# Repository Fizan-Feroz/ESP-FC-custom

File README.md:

# ESP-FC Flight Controller

The mini, DIY, Low cost, ESP32 based, high performance flight controller for hobbyists.

# Features

* Espressif targets (ESP32, ESP32-S3)
* ESC protocols (PWM, Oneshot125/42, Multishot, Brushed, Dshot150/300/600 bidirectional)
* PPM, SBUS, IBUS and CRSF Receivers
* Builtin ESP-NOW receiver and WiFi configuration [read more...](/docs/wireless.md)
* SPI and I2C gyro modules support (MPU6050, MPU9250, ICM20602, ICM42688, BMI160)
* Flight modes (ACRO, ANGLE, AIRMODE)
* Frames (Quad X)
* Betaflight configuration tool compatible (v10.10)
* Configurable Gyro Filters (LPF, Dynamic Notches, dTerm, RPM)
* Blackbox recording (OpenLog/OpenLager/Flash)
* Up to 4kHz gyro/loop on ESP32 with SPI gyro
* MSP and CLI protocol interface
* Resorce/Pin mapping
* In flight PID Tuning
* Buzzer, Led and voltage monitor
* Failsafe mode

# Documentation

In this repository you can find firmware code that allows you to build your own flight controller. For convenience it mimics Betaflight 4.2 compability, so that it can be configured using [betaflight-configurator](https://github.com/betaflight/betaflight-configurator). Also [online blackbox-log-viewer](https://blackbox.betaflight.com/) can be used to analyze blackbox logs. In most aspects it is similar to Betaflight, so that many configuration and tuning advices are helpfull here too. But you must be aware, that this software is not the same as Betaflight, there are some limitations and differences in functionality and performance.

> [!IMPORTANT]
> Before you begin, **read the following documentation carefully first!**.

 * [Setup Guide](/docs/setup.md)
 * [Hardware & Custom PCB Guide](/docs/hardware.md)
 * [Wiring](/docs/wiring.md)
 * [CLI Commands](/docs/cli.md)
 * [WIFI and ESP-NOW Receiver](/docs/wireless.md)

Join our **[Discord Channel](https://discord.gg/jhyPPM5UEH)** to get help

# Quick Start

## Requirements

Hardware:
* ESP32 or ESP32-S3 board
* MPU9250 SPI or MPU6050 I2C gyro (GY-88, GY-91, GY-521 or similar)
* PDB with 5V BEC
* Buzzer and some electronic components (optional).

Software:
* [Betaflight Configurator](https://github.com/betaflight/betaflight-configurator/releases) (v10.10)
* [CH340 usb-serial converter driver](https://sparks.gogo.co.nz/ch340.html)

## Flashing

1. Download and unpack selected firmware from [Releases Page](https://github.com/rtlopez/esp-fc/releases)
2. Visit [ESP Tool Website](https://espressif.github.io/esptool-js/)
3. Click "Connect" and choose device port in dialog
4. Add firmware file and set Flash Address to `0x00`
5. Click "Program"
6. After success power cycle board

## Setup

After flashing you need to configure few things first:

 1. Configure pinout according to your wiring, especially pin functions, you can find more information in [CLI Reference](/docs/cli.md)
 2. Connect to [Betaflight Configurator](https://github.com/betaflight/betaflight-configurator/releases) and setup to your preferences,
 3. Test motors without propellers
 4. Have fun ;)

> [!NOTE]
> Not all functions displayed in configurator are avalable in firmware. The rule of thumb is if you cannot change specific option in Betaflight Configurator, that means it is not supported. It usually rolls back to previous value after save. It is strongly recommended to follow [setup guide](/docs/setup.md).

## Wiring diagrams

## Supported Modules

 * **ESP32** - recommended
 * **ESP32-S3** - recommended
 * **ESP32-S2** - experimantal
 * **ESP32-C3** - experimantal, lack of performance, no FPU
 * **RP2350** - experimantal, partially works
 * **RP2040** - experimantal, lack of performance, no FPU
 * **ESP8266** - obsolete, no longer developed

## Supported Sensors and Protocols

 * Gyro: MPU6050, MPU6000, MPU6500, MPU9250, ICM20602, ICM42688, BMI160
 * Barometers: BMP180, BMP280, SPL06
 * Magnetometers: HMC5883, QMC5883, AK8963, QMC5883P
 * Receivers: PPM, SBUS, IBUS, CRSF/ELRS
 * Esc Protocols: PWM, BRUSHED, ONESHOT125, ONESHOT42, MULTISHOT, DSHOT150, DSHOT300, DSHOT600
 * GPS: M8, M9, F9 & M10(dual band, all constellations configurable by cli)
 * Other protocols: MSP, CLI, BLACKBOX, ESPNOW

## Issues

You can report issues using Github [tracker](https://github.com/rtlopez/esp-fc/issues). 
You can also join our [Discord Channel](https://discord.gg/jhyPPM5UEH)

## Development

* Visual Studio Code
* [PlatformIO](https://platformio.org/install/ide?install=vscode) extension
* Git

## Todo

* Altitude Hold
* GPS Navigation
* MS5611 barometer
* Balancing robot controller

## Licence

This project is distributed under MIT Licence. Bear in mind that:

THE SOFTWARE IS PROVIDED "AS IS", WITHOUT WARRANTY OF ANY KIND, EXPRESS OR
IMPLIED, INCLUDING BUT NOT LIMITED TO THE WARRANTIES OF MERCHANTABILITY,
FITNESS FOR A PARTICULAR PURPOSE AND NONINFRINGEMENT. IN NO EVENT SHALL THE
AUTHORS OR COPYRIGHT HOLDERS BE LIABLE FOR ANY CLAIM, DAMAGES OR OTHER
LIABILITY, WHETHER IN AN ACTION OF CONTRACT, TORT OR OTHERWISE, ARISING FROM,
OUT OF OR IN CONNECTION WITH THE SOFTWARE OR THE USE OR OTHER DEALINGS IN THE
SOFTWARE.

## Donations
If you like this project and you want it to be still developed, you can support me a little.

* BTC: 1Lopez7yPtbyjfLGe892JfheDFJMMt43tW
* LTC: LV3G3sJxz9AYpDMYUp8e1LCmerFYxVY3ak

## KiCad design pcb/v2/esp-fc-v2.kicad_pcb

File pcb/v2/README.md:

# ESP-FC v2 Flight Controller PCB

Revision 2 of the custom 30.5x30.5mm 4-layer flight controller PCB for the **ESP-FC** flight control firmware.

---

## 1. Revision Highlights & Changelog (v2)

* **TVS Diode Upgrade (D1)**: Upgraded from `SMAJ20A` to **`SMAJ28A`** (400W unidirectional, 28V standoff voltage). Safely accommodates 6S LiPo batteries (up to 25.2V nominal charge + flyback margin) without false clamping or thermal breakdown during active braking.
* **100% Complete Routing**:
  * `UART1_RX` (GPIO 16) routed cleanly to J3 (Pin 3).
  * `UART1_TX` (GPIO 17) routed cleanly to J3 (Pin 4).
  * `I2C_SDA` (GPIO 21) routed cleanly between ESP32, pull-up resistor R11, and external I2C header J4.
* **DRC Verification**:
  * **0 unconnected items**
  * **0 electrical clearance errors**
  * **0 shorting errors**
  * Fully compliant with standard JLCPCB / PCBWay manufacturing rules (min clearance: 0.15mm, power: 0.20mm, min via: 0.45mm / 0.20mm drill).
* **Production Gerbers**:
  * Generated and packaged in `esp-fc-v2-gerbers.zip`.

---

## 2. Specifications

| Parameter | Specification | Notes |
| :--- | :--- | :--- |
| **MCU** | Espressif ESP32-WROOM-32E | Dual-core 240MHz, 4MB Flash |
| **Form Factor** | 36.0 x 36.0 mm outer | Standard 30.5 x 30.5 mm M3 mounting holes |
| **Layer Stackup** | 4-Layer FR4 (1.6mm thickness) | L1: Signals/RF, L2: GND Plane, L3: Power Planes, L4: Signals/Power |
| **Copper Weight** | 1 oz outer / 1 oz inner | 35µm copper thickness |
| **Input Voltage** | 2S - 6S LiPo (7.4V - 25.2V) | D1 TVS clamping: SMAJ28A |
| **5V BEC** | Synchronous Buck 5V @ 2A | Powers receiver, buzzer, GPS, and LDO |
| **3.3V LDO** | Low-noise LDO 3.3V @ 500mA | Powers ESP32 and onboard IMU |
| **IMU** | InvenSense MPU-6000 / MPU-6500 | Dedicated SPI bus + external modular 1x8 IMU header |
| **Connectors** | JST-SH 1.0mm 8-pin (ESC) | Standard 4-in-1 ESC pinout with telemetry & current sense |
| | JST-SH 1.0mm 4-pin (UART1/GPS) | 5V, GND, RX1, TX1 |
| | JST-SH 1.0mm 4-pin (I2C/Mag/Baro) | 3.3V, GND, SCL, SDA |
| | USB Type-C | CH340C auto-reset programming interface |

---

## 3. Manufacturing & Ordering Guide (JLCPCB / PCBWay)

Upload `esp-fc-v2-gerbers.zip` directly to the PCB manufacturer with the following parameters:

* **Dimensions**: 36.0 mm x 36.0 mm
* **Layers**: 4
* **PCB Thickness**: 1.6 mm
* **Impedance Control**: No (or standard JLC04161H-7628 stackup)
* **Surface Finish**: ENIG (recommended for QFN MPU-6000) or HASL-lead-free
* **Copper Weight**: 1 oz outer / 1 oz inner
* **Solder Mask**: Matte Black or Blue
* **Silkscreen**: White
* **Minimum Track/Clearance**: 0.15mm / 0.15mm (6/6 mil)
* **Minimum Via Hole Size**: 0.20mm (via diameter 0.45mm)

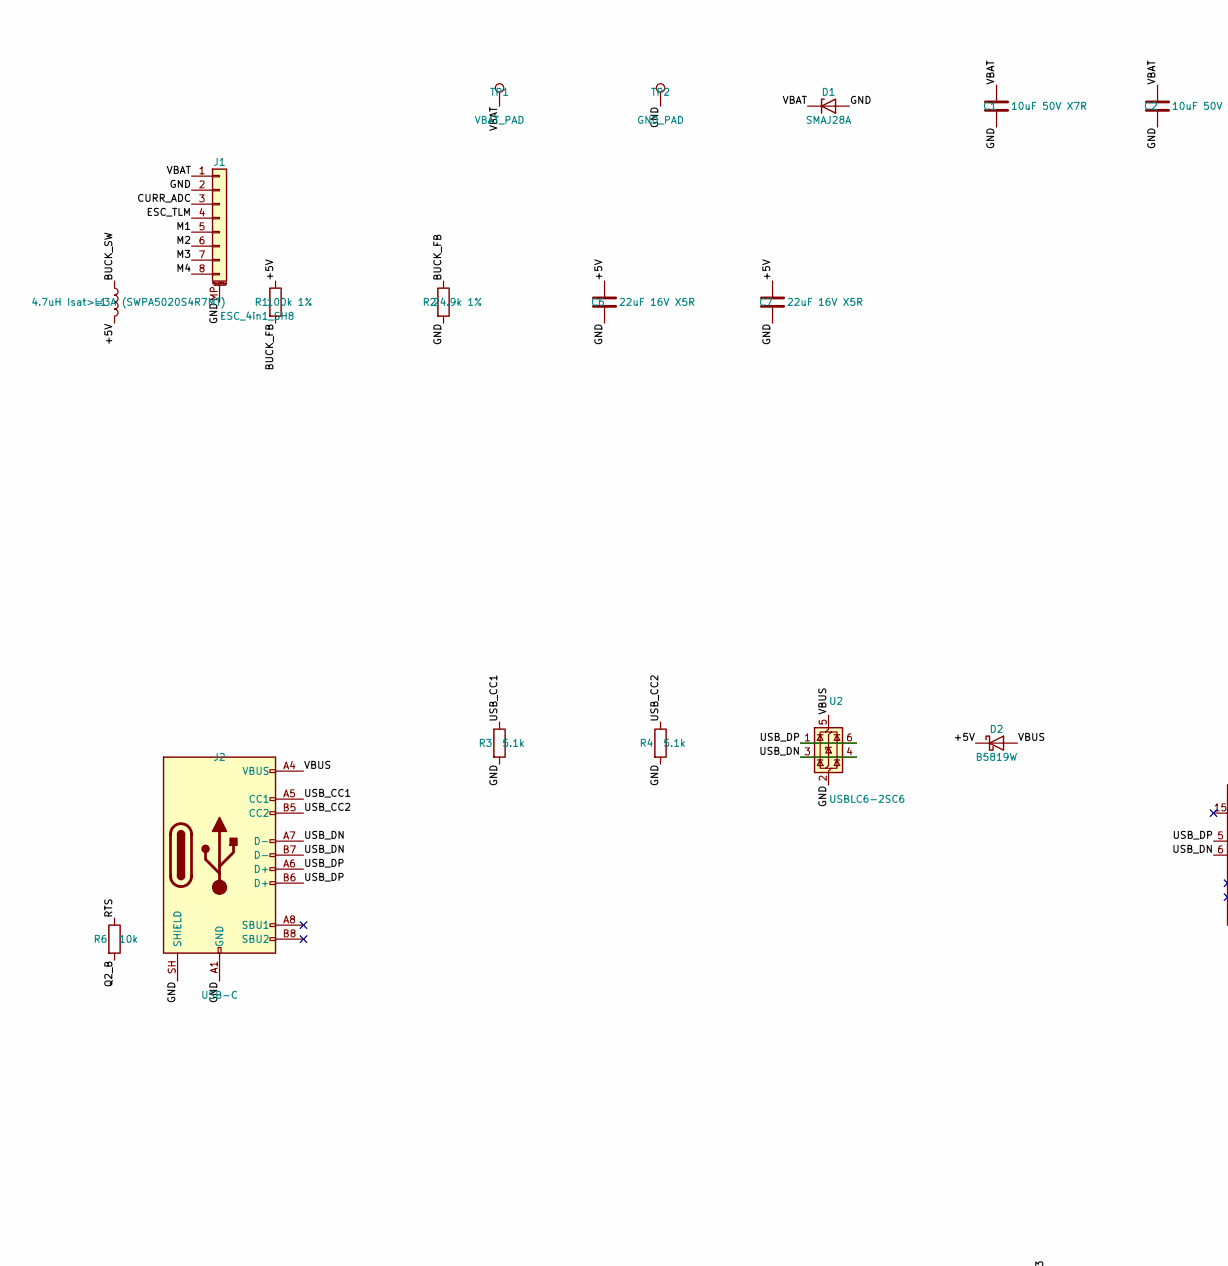
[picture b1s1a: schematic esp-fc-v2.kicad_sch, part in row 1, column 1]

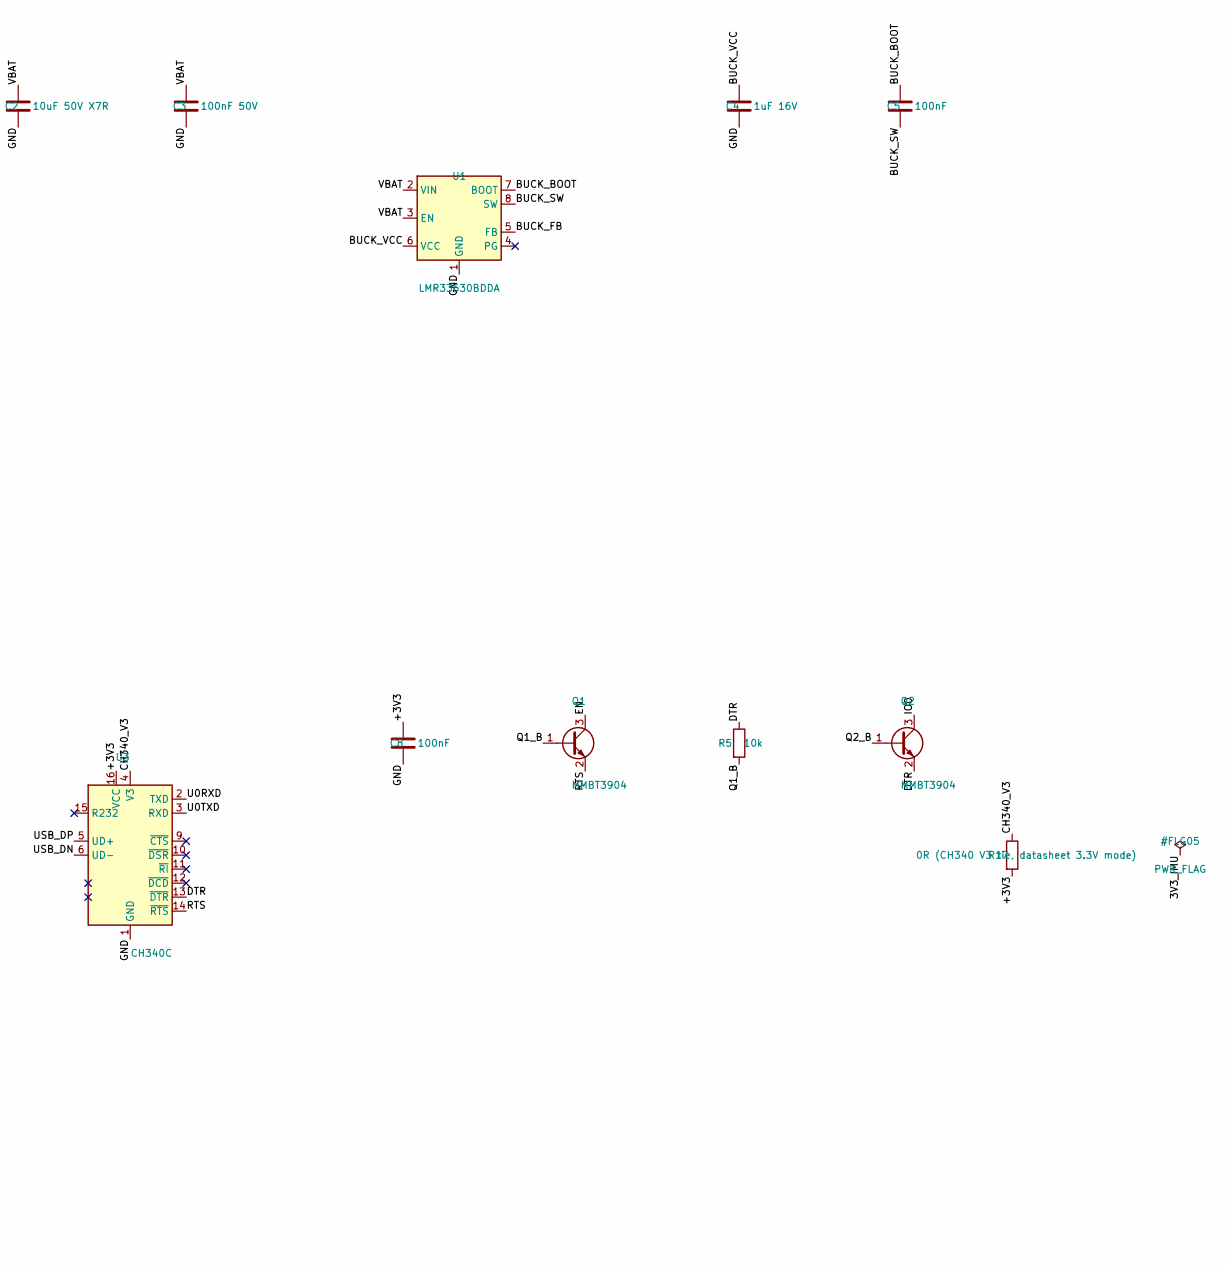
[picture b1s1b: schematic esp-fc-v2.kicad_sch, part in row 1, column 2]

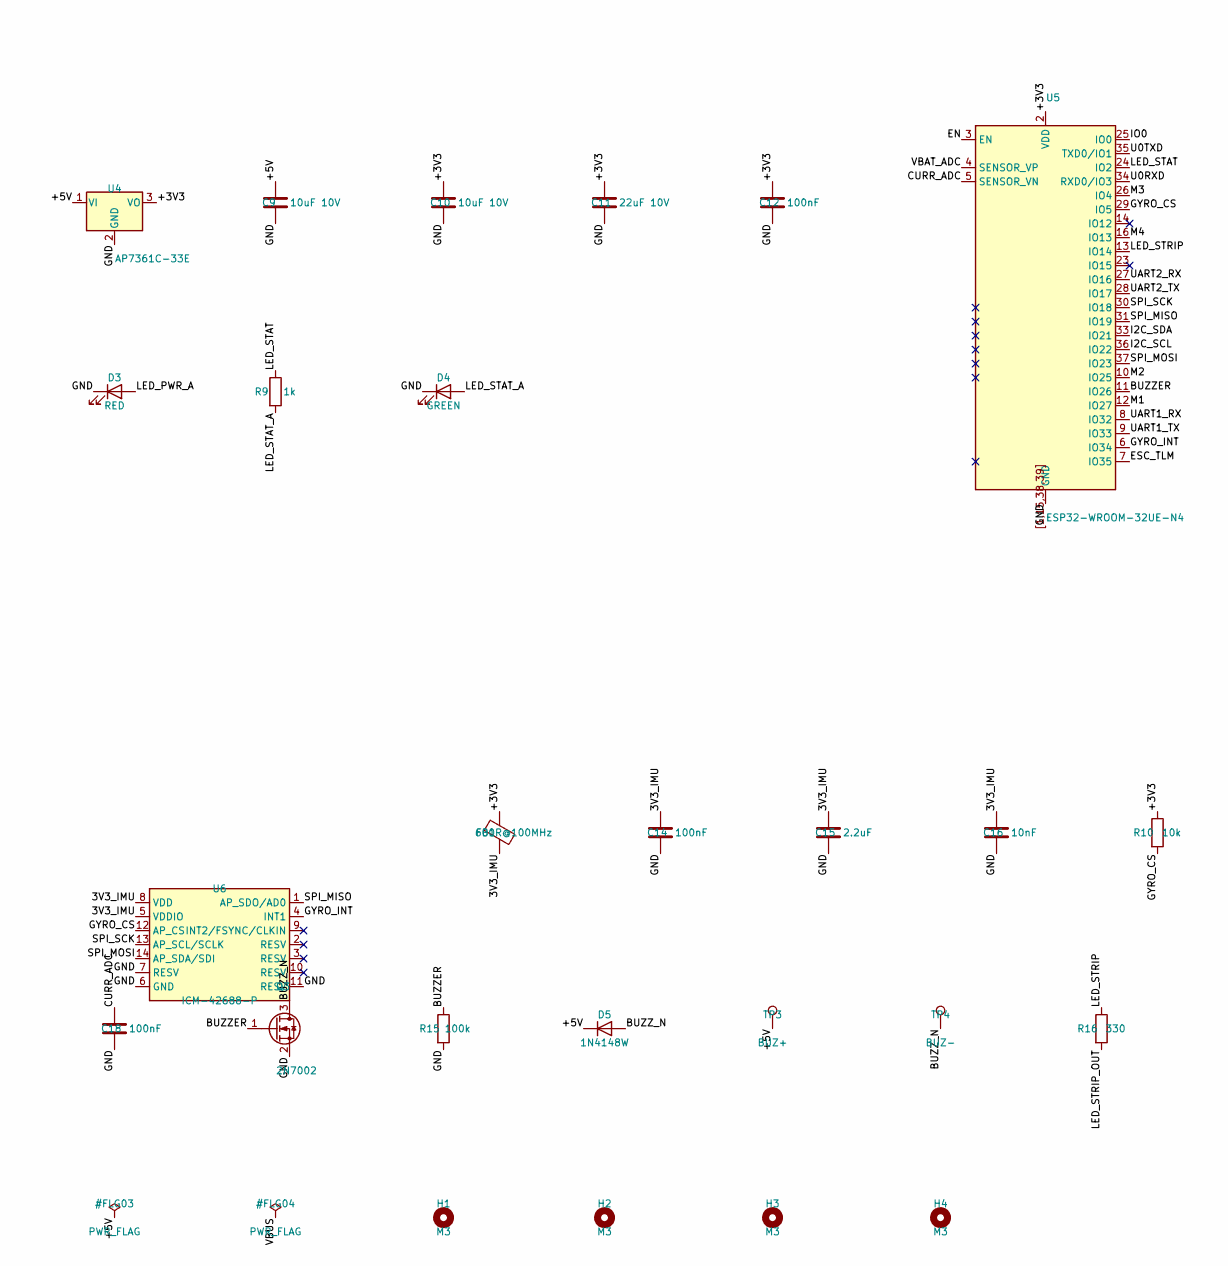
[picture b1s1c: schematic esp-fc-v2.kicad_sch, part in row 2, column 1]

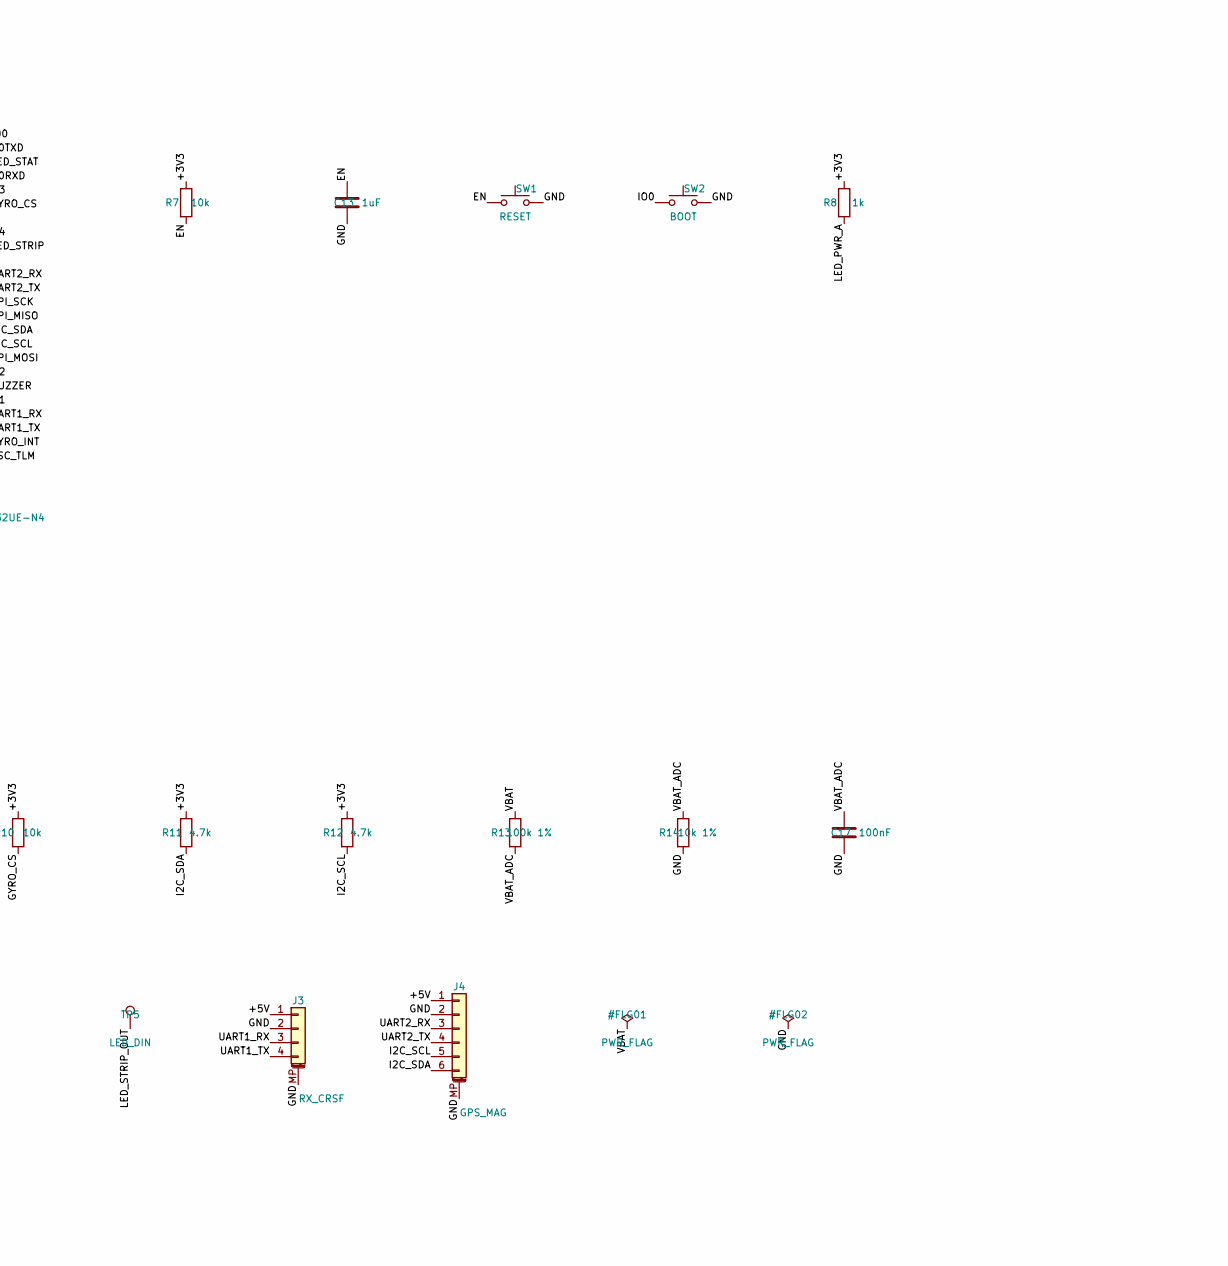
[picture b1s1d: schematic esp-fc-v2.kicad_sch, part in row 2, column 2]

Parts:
C1, C2: 10uF 50V X7R; C_1206_3216Metric
C3: 100nF 50V; C_0603_1608Metric
C4: 1uF 16V; C_0603_1608Metric
C5, C8, C12, C14, C17, C18: 100nF; C_0603_1608Metric
C6, C7: 22uF 16V X5R; C_1206_3216Metric
C9, C10: 10uF 10V; C_0805_2012Metric
C11: 22uF 10V; C_0805_2012Metric
C13: 1uF; C_0603_1608Metric
C15: 2.2uF; C_0603_1608Metric
C16: 10nF; C_0603_1608Metric
D1: SMAJ28A; D_SMA
D2: B5819W; D_SOD-123
D3: RED; LED_0603_1608Metric
D4: GREEN; LED_0603_1608Metric
D5: 1N4148W; D_SOD-323
FB1: 600R@100MHz; L_0603_1608Metric
H1, H2, H3, H4: M3; MountingHole_3.2mm_M3
J1: ESC_4in1_SH8; JST_SH_SM08B-SRSS-TB_1x08-1MP_P1.00mm_Horizontal
J2: USB-C; USB_C_Receptacle_HRO_TYPE-C-31-M-12
J3: RX_CRSF; JST_SH_SM04B-SRSS-TB_1x04-1MP_P1.00mm_Horizontal
J4: GPS_MAG; JST_SH_SM06B-SRSS-TB_1x06-1MP_P1.00mm_Horizontal
L1: 4.7uH Isat>=3A (SWPA5020S4R7MT); L_Sunlord_SWPA5020S
Q1, Q2: MMBT3904; SOT-23
Q3: 2N7002; SOT-23
R1, R13: 100k 1%; R_0603_1608Metric
R2: 24.9k 1%; R_0603_1608Metric
R3, R4: 5.1k; R_0603_1608Metric
R5, R6, R7, R10: 10k; R_0603_1608Metric
R8, R9: 1k; R_0603_1608Metric
R11, R12: 4.7k; R_0603_1608Metric
R14: 10k 1%; R_0603_1608Metric
R15: 100k; R_0603_1608Metric
R16: 330; R_0603_1608Metric
R17: 0R (CH340 V3 tie, datasheet 3.3V mode); R_0603_1608Metric
SW1: RESET; SW_Push_1P1T_NO_CK_KMR2
SW2: BOOT; SW_Push_1P1T_NO_CK_KMR2
TP1: VBAT_PAD; TestPoint_Pad_2.5x2.5mm
TP2: GND_PAD; TestPoint_Pad_2.5x2.5mm
TP3: BUZ+; TestPoint_Pad_1.5x1.5mm
TP4: BUZ-; TestPoint_Pad_1.5x1.5mm
TP5: LED_DIN; TestPoint_Pad_1.5x1.5mm
U1: LMR33630BDDA; Texas_HSOP-8-1EP_3.9x4.9mm_P1.27mm_ThermalVias
U2: USBLC6-2SC6; SOT-23-6
U3: CH340C; SOIC-16_3.9x9.9mm_P1.27mm
U4: AP7361C-33E; SOT-223-3_TabPin2
U5: ESP32-WROOM-32UE-N4; ESP32-WROOM-32UE
U6: ICM-42688-P; LGA-14_3x2.5mm_P0.5mm_LayoutBorder3x4y

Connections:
3V3_IMU: C14.1, C15.1, C16.1, FB1.2, U6.5 (VDDIO), U6.8 (VDD)
+3V3: C8.1, C10.1, C11.1, C12.1, FB1.1, R7.1, R8.1, R10.1, R11.1, R12.1, R17.2, U3.16 (VCC), U4.3 (VO), U5.2 (VDD)
+5V: C6.1, C7.1, C9.1, D2.1 (K), D5.1 (K), J3.1, J4.1, L1.2, R1.1, TP3.1, U4.1 (VI)
BUCK_BOOT: C5.1, U1.7 (BOOT)
BUCK_FB: R1.2, R2.1, U1.5 (FB)
BUCK_SW: C5.2, L1.1, U1.8 (SW)
BUCK_VCC: C4.1, U1.6 (VCC)
BUZZER: Q3.1 (G), R15.1, U5.11 (IO26)
BUZZ_N: D5.2 (A), Q3.3 (D), TP4.1
CH340_V3: R17.1, U3.4 (V3)
CURR_ADC: C18.1, J1.3, U5.5 (SENSOR_VN)
DTR: Q2.2 (E), R5.1, U3.13 (~DTR)
EN: C13.1, Q1.3 (C), R7.2, SW1.1, U5.3 (EN)
ESC_TLM: J1.4, U5.7 (IO35)
GND: C1.2, C2.2, C3.2, C4.2, C6.2, C7.2, C8.2, C9.2, C10.2, C11.2, C12.2, C13.2, C14.2, C15.2, C16.2, C17.2, C18.2, D1.2 (A), D3.1 (K), D4.1 (K), J1.2, J1.MP (MountPin), J2.A1 (GND), J2.A12 (GND), J2.B1 (GND), J2.B12 (GND), J2.SH (SHIELD), J3.2, J3.MP (MountPin), J4.2, J4.MP (MountPin), Q3.2 (S), R2.2, R3.2, R4.2, R14.2, R15.2, SW1.2, SW2.2, TP2.1, U1.1 (GND), U1.9 (GND), U2.2 (GND), U3.1 (GND), U4.2 (GND), U5.1, U5.15, U5.38, U5.39, U5.[1,15,38,39] (GND), U6.6 (GND), U6.7 (RESV), U6.11 (RESV)
GYRO_CS: R10.2, U5.29 (IO5), U6.12 (AP_CS)
GYRO_INT: U5.6 (IO34), U6.4 (INT1)
I2C_SCL: J4.5, R12.2, U5.36 (IO22)
I2C_SDA: J4.6, R11.2, U5.33 (IO21)
IO0: Q2.3 (C), SW2.1, U5.25 (IO0)
LED_PWR_A: D3.2 (A), R8.2
LED_STAT: R9.1, U5.24 (IO2)
LED_STAT_A: D4.2 (A), R9.2
LED_STRIP: R16.1, U5.13 (IO14)
LED_STRIP_OUT: R16.2, TP5.1
M1: J1.5, U5.12 (IO27)
M2: J1.6, U5.10 (IO25)
M3: J1.7, U5.26 (IO4)
M4: J1.8, U5.16 (IO13)
Q1_B: Q1.1 (B), R5.2
Q2_B: Q2.1 (B), R6.2
RTS: Q1.2 (E), R6.1, U3.14 (~RTS)
SPI_MISO: U5.31 (IO19), U6.1 (AP_SDO/AD0)
SPI_MOSI: U5.37 (IO23), U6.14 (AP_SDA/SDI)
SPI_SCK: U5.30 (IO18), U6.13 (AP_SCL/SCLK)
U0RXD: U3.2 (TXD), U5.34 (RXD0/IO3)
U0TXD: U3.3 (RXD), U5.35 (TXD0/IO1)
UART1_RX: J3.3, U5.8 (IO32)
UART1_TX: J3.4, U5.9 (IO33)
UART2_RX: J4.3, U5.27 (IO16)
UART2_TX: J4.4, U5.28 (IO17)
USB_CC1: J2.A5 (CC1), R3.1
USB_CC2: J2.B5 (CC2), R4.1
USB_DN: J2.A7 (D-), J2.B7 (D-), U2.3 (I/O2), U2.4 (I/O2), U3.6 (UD-)
USB_DP: J2.A6 (D+), J2.B6 (D+), U2.1 (I/O1), U2.6 (I/O1), U3.5 (UD+)
VBAT: C1.1, C2.1, C3.1, D1.1 (K), J1.1, R13.1, TP1.1, U1.2 (VIN), U1.3 (EN)
VBAT_ADC: C17.1, R13.2, R14.1, U5.4 (SENSOR_VP)
VBUS: D2.2 (A), J2.A4 (VBUS), J2.A9 (VBUS), J2.B4 (VBUS), J2.B9 (VBUS), U2.5 (VBUS)

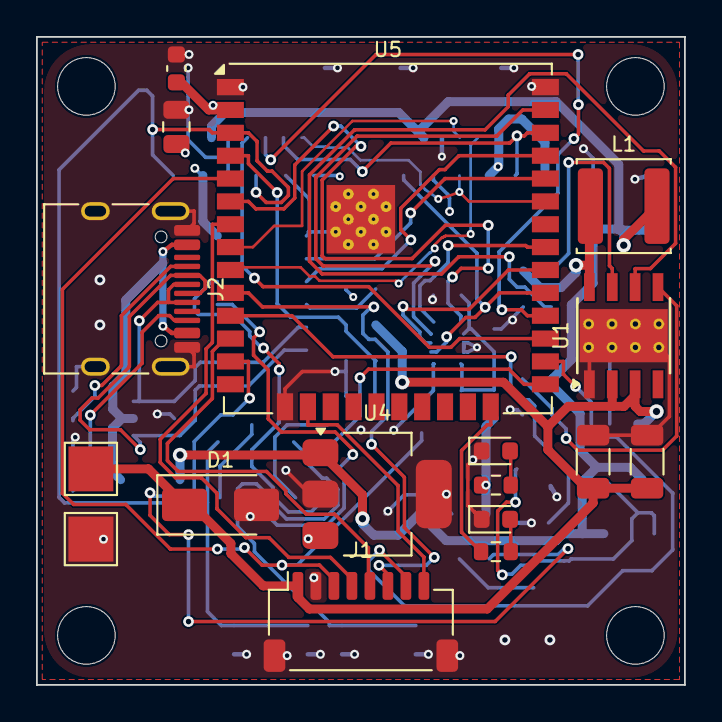
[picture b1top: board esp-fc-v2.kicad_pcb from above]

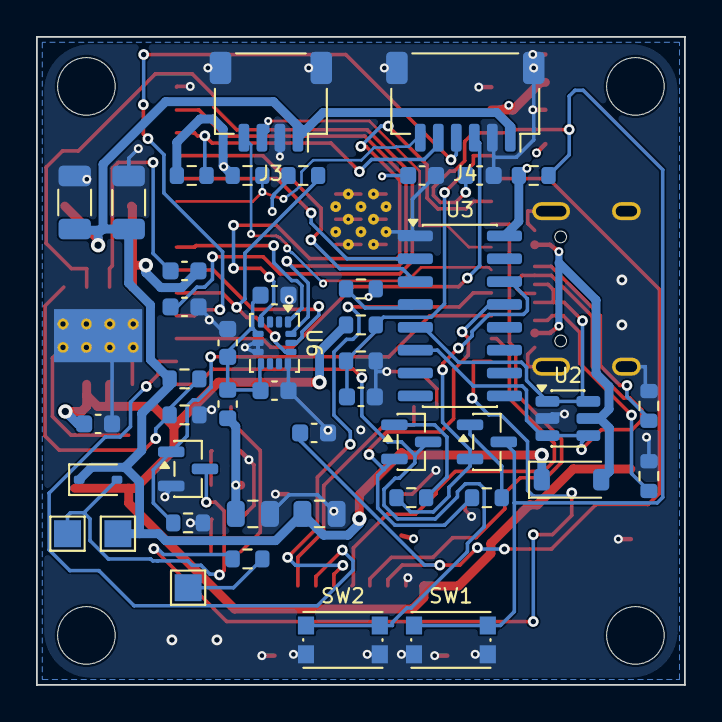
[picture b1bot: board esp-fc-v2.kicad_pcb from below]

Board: 4 copper layers, 36.0 x 36.0 mm, 66 parts (45 on the bottom side), 48 nets.

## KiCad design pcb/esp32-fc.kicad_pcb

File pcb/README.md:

# ESP-FC 30.5x30.5mm Flight Controller PCB

A high-performance, 4-layer drone flight controller designed for the **ESP-FC** firmware, powered by an **ESP32-WROOM-32E** (dual-core 240MHz with Wi-Fi / ESP-NOW telemetry) in a standard **30.5 × 30.5 mm M3** stack form factor.

---

## 1. Specifications & Features

* **MCU**: Espressif **ESP32-WROOM-32E** (Dual-core Xtensa 240MHz, 4MB Flash, integrated antenna overhang).
* **Form Factor**: 36.0 × 36.0 mm outer dimension, **30.5 × 30.5 mm M3** mounting holes (standard 4-in-1 ESC stack).
* **Stackup**: 4-layer high-speed PCB:
  * `Layer 1 (Top / F.Cu)`: RF & high-speed SPI bus routing, status LEDs, primary ICs.
  * `Layer 2 (Inner 1 / In1.Cu)`: Dedicated, unbroken **Ground Plane** (noise isolation for IMU).
  * `Layer 3 (Inner 2 / In2.Cu)`: Power planes (5V, 3.3V, VBAT).
  * `Layer 4 (Bottom / B.Cu)`: Motor pads, ESC harness connector, USB-UART bridge, solder pads.
* **Sensors**:
  * **Primary Onboard IMU**: InvenSense **MPU-6000 / MPU-6500** (QFN-24) connected via high-speed SPI bus (up to 4kHz loop rate).
  * **Dual IMU Support**: Dedicated 1×8 (2.54mm) breakout header for modular external sensors (GY-521, GY-91, GY-88, ICM-42688-P).
  * **I2C Bus**: Dedicated 4-pin port for external Barometer (BMP280 / SPL06) and GPS Magnetometer (QMC5883L).
* **Power Management**:
  * **Input Voltage**: 2S – 6S LiPo (7.4V – 25.2V) with TVS voltage-spike suppression diode (SMAJ28A).
  * **5V BEC**: Synchronous step-down buck converter (SY8120B / MP2359) delivering **5V @ 2A**.
  * **3.3V LDO**: Ultra-low-noise linear regulator (ME6211C33 / AP2112K-3.3, 500mA) dedicated to ESP32 and sensitive IMU.
  * **Power OR-ing**: BAT54C Schottky diode for seamless automatic power switching between USB and LiPo.
* **ESC & Motor Outputs**:
  * Standard JST-SH 8-pin 1.0mm 4-in-1 ESC connector (GND, VBAT, M1, M2, M3, M4, CURR, TELEM).
  * 4 corner high-current solder pads for direct ESC motor signal wiring (DShot150/300/600 & PWM).
* **USB & Flashing**:
  * USB Type-C connector with 5.1kΩ CC1/CC2 pull-downs.
  * Onboard CH340C USB-to-UART bridge.
  * Automatic bootloader / reset circuit (UMH3N dual-NPN) for one-click flashing via PlatformIO or Web ESP-Tool.

---

## 2. Hardware Pinout Table (Firmware Aligned)

| Signal Name | ESP32 GPIO | Description / Destination |
| :--- | :---: | :--- |
| **M1** (Motor 1) | `GPIO 27` | Front-Right Motor / ESC Signal 1 |
| **M2** (Motor 2) | `GPIO 25` | Rear-Right Motor / ESC Signal 2 |
| **M3** (Motor 3) | `GPIO 4` | Rear-Left Motor / ESC Signal 3 |
| **M4** (Motor 4) | `GPIO 12` | Front-Left Motor / ESC Signal 4 |
| **SPI_SCK** | `GPIO 18` | Hardware SPI Clock -> Onboard MPU & IMU Header |
| **SPI_MISO** | `GPIO 19` | Hardware SPI MISO -> Onboard MPU & IMU Header |
| **SPI_MOSI** | `GPIO 23` | Hardware SPI MOSI -> Onboard MPU & IMU Header |
| **SPI_CS0** | `GPIO 5` | Gyro Chip Select (`pin_spi_cs_0`) |
| **GYRO_INT** | `GPIO 34` | Gyro Data Ready Interrupt (Input only) |
| **I2C_SDA** | `GPIO 21` | I2C Data (Compass / Baro) with 4.7kΩ pull-up |
| **I2C_SCL** | `GPIO 22` | I2C Clock (Compass / Baro) with 4.7kΩ pull-up |
| **UART0_TX** | `GPIO 1` | USB Serial CLI / MSP / Betaflight Configurator |
| **UART0_RX** | `GPIO 3` | USB Serial CLI / MSP / Betaflight Configurator |
| **UART1_RX** | `GPIO 32` | CRSF / ELRS / SBUS Receiver RX |
| **UART1_TX** | `GPIO 33` | CRSF / ELRS Receiver Telemetry TX |
| **UART2_RX** | `GPIO 16` | GPS Module RX2 / Blackbox Logger |
| **UART2_TX** | `GPIO 17` | GPS Module TX2 / Blackbox Logger |
| **VBAT_ADC** | `GPIO 36` | LiPo Voltage Divider (100kΩ / 10kΩ, 11:1 scale) |
| **CURR_ADC** | `GPIO 39` | Current Sensor input from 4-in-1 ESC |
| **BUZZER** | `GPIO 26` | Active Buzzer driver (N-MOSFET 2N7002) |
| **LED_STAT** | `GPIO 2` | Status Indicator LED (Green) |
| **BOOT** | `GPIO 0` | Boot Switch / Auto-download circuit |
| **EN / RST** | `EN` | Chip Reset with 10kΩ pull-up and 1µF debounce |

---

## 3. Directory Contents

* **`esp32-fc.kicad_pcb`**: 4-layer KiCad PCB layout file with exact 30.5×30.5mm M3 geometry, footprint placement, and silkscreen markings.
* **`esp32-fc.kicad_pro`**: KiCad 10 project settings with net classes (`Default` and `Power`).
* **`build_fc_pcb.py`**: Python script that builds and automates board geometry via KiCad 10's native `pcbnew` API.
* **`esp32_fc_top_render.png`**: High-resolution 3D ray-traced render of the top board assembly.
* **`esp32_fc_bottom_render.png`**: High-resolution 3D ray-traced render of the bottom board assembly.
* **`gerbers/`**: Complete fabrication archive (Gerber RS-274X and Excellon Drill files) ready for JLCPCB / PCBWay manufacturing.

---

## 4. Bill of Materials (BOM)

| Ref Des | Component / Value | Package | Recommended Part Number |
| :--- | :--- | :--- | :--- |
| **U1** | ESP32-WROOM-32E (4MB) | Module SMD | Espressif ESP32-WROOM-32E-N4 |
| **U2** | MPU-6000 or MPU-6500 | QFN-24 (4×4mm, 0.5mm pitch) | InvenSense MPU-6000 / MPU-6500 |
| **U3** | CH340C USB-to-UART | SOIC-16 (1.27mm pitch) | WCH CH340C (internal clock) |
| **U4** | 5V 2A Synchronous Buck | SOT-23-6 | Silergy SY8120B / MPS MP2359 |
| **U5** | 3.3V 500mA Low-Noise LDO | SOT-23-5 | MicrOne ME6211C33M5G / Diodes AP2112K-3.3 |
| **L1** | 4.7µH 3A Power Inductor | SMD 0805 / 2012 | Sunlord SWPA4020S4R7MT |
| **D_TVS**| 28V 400W TVS Diode | SMA / DO-214AC | Littelfuse SMAJ28A |
| **D_OR** | Dual Schottky Barrier Diode | SOT-23 | Diodes Inc BAT54C |
| **Q_BUZ**| 60V 300mA N-MOSFET | SOT-23 | ON Semi 2N7002 / AO3400 |
| **C_IN1**| 10µF 50V X7R Ceramic | 0805 | Murata GRM21BR71H106KE43L |
| **C_OUT1**| 22µF 10V X5R Ceramic | 0805 | Samsung CL21A226MPCLRNC |
| **J_ESC**| 8-Pin 1.0mm SMD Horizontal | JST-SH 8P | JST SM08B-SRSS-TB |
| **H1-H4**| M3 Mounting Holes (3.2mm ID, 6.0mm OD) | Pad via annular ring | Standard 30.5×30.5mm M3 |

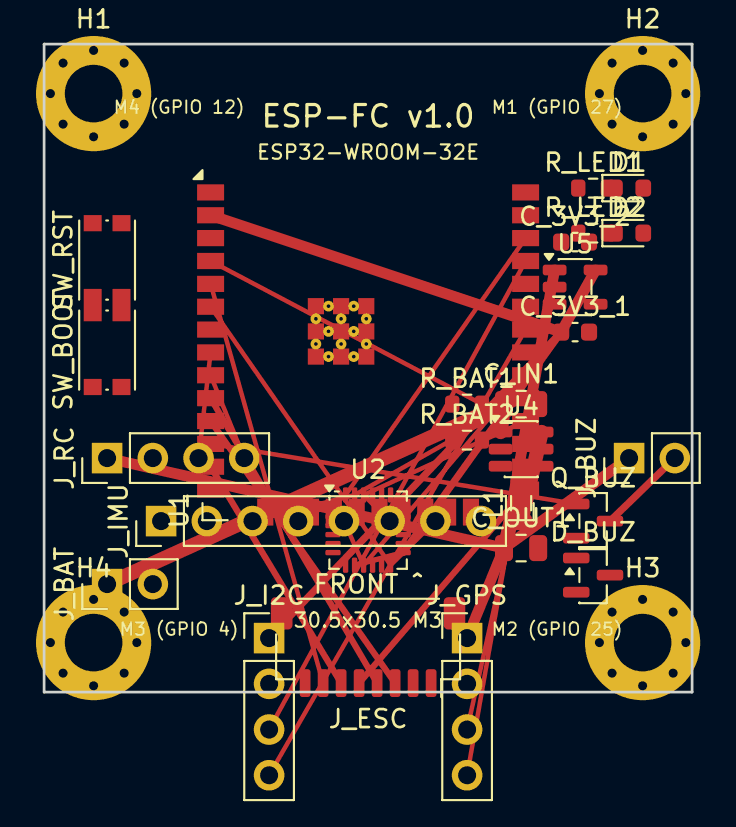
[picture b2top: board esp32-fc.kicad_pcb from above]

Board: 4 copper layers, 36.0 x 36.0 mm, 31 parts (1 on the bottom side), 23 nets.

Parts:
C_3V3_1: 10uF; C_0603_1608Metric
C_3V3_2: 100nF; C_0603_1608Metric
C_IN1: 10uF_50V; C_0805_2012Metric
C_OUT1: 22uF_10V; C_0805_2012Metric
D1: LED_PWR_RED; LED_0603_1608Metric
D2: LED_STAT_GRN; LED_0603_1608Metric
D_BUZ: BAT54; SOT-23
H1, H2, H3, H4: M3_Mount; MountingHole_3.2mm_M3_Pad_Via
J_BAT: VBAT_2S-6S; PinHeader_1x02_P2.54mm_Vertical
J_BUZ: BUZZER; PinHeader_1x02_P2.54mm_Vertical
J_ESC: 4-IN-1_ESC; JST_SH_SM08B-SRSS-TB_1x08-1MP_P1.00mm_Horizontal
J_GPS: GPS_TELEM; PinHeader_1x04_P2.54mm_Vertical
J_I2C: I2C_BARO_MAG; PinHeader_1x04_P2.54mm_Vertical
J_IMU: IMU_Breakout; PinHeader_1x08_P2.54mm_Vertical
J_RC: ELRS_CRSF; PinHeader_1x04_P2.54mm_Vertical
L1: 4.7uH; L_0805_2012Metric
Q_BUZ: 2N7002; SOT-23
R_BAT1: 100k_1%; R_0603_1608Metric
R_BAT2: 10k_1%; R_0603_1608Metric
R_LED1, R_LED2: 1k; R_0603_1608Metric
SW_BOOT: BOOT; SW_Push_1P1T_NO_CK_KMR2
SW_RST: RESET; SW_Push_1P1T_NO_CK_KMR2
U1: ESP32-WROOM-32E
U2: MPU-6000/6500; InvenSense_QFN-24_4x4mm_P0.5mm
U3: CH340C; SOIC-16_3.9x9.9mm_P1.27mm
U4: SY8120B_5V2A; SOT-23-6
U5: ME6211C33; SOT-23-5

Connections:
+3V3: C_3V3_1.1, C_3V3_2.1, J_I2C.1, J_IMU.1, J_IMU.8, U1.2, U2.8, U2.13, U5.5
+5V: C_OUT1.1, J_BUZ.1, J_GPS.1, J_RC.1, L1.1, L1.2, U4.6, U5.1
BUZZER: Q_BUZ.1, U1.12
BUZZER-: J_BUZ.2, Q_BUZ.3
CURR_ADC: J_ESC.7, U1.5
GND: C_3V3_1.2, C_3V3_2.2, C_IN1.2, C_OUT1.2, H1.1, H2.1, H3.1, H4.1, J_BAT.2, J_ESC.1, J_GPS.2, J_I2C.2, J_IMU.2, J_RC.2, Q_BUZ.2, R_BAT2.2, U1.1, U1.7, U1.14, U1.15, U1.16, U1.17, U1.18, U1.19, U1.20, U1.21, U1.22, U1.31, U1.37, U1.38, U1.39, U2.1, U2.11, U2.18, U4.2, U5.2
GYRO_INT: J_IMU.7, U1.6, U2.12
I2C_SCL: J_I2C.3, U1.35
I2C_SDA: J_I2C.4, U1.32
MOTOR_1: J_ESC.3, U1.11
MOTOR_2: J_ESC.4, U1.10
MOTOR_3: J_ESC.5, U1.25
MOTOR_4: J_ESC.6, U1.13
SPI_CS0: J_IMU.6, U1.28, U2.22
SPI_MISO: J_IMU.5, U1.30, U2.9
SPI_MOSI: J_IMU.4, U1.36, U2.24
SPI_SCK: J_IMU.3, U1.29, U2.23
UART1_RX: J_RC.3, U1.8
UART1_TX: J_RC.4, U1.9
UART2_RX: J_ESC.8, J_GPS.3, U1.26
UART2_TX: J_GPS.4, U1.27
VBAT: C_IN1.1, J_BAT.1, J_ESC.2, R_BAT1.1, U4.1
VBAT_ADC: R_BAT1.2, R_BAT2.1, U1.4
